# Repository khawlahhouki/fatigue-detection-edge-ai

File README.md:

#Real-Time Physical Fatigue Detection — Edge AI on STM32H7

> **Final Year Project (PFE) — ENICarthage, 2026**  
> Embedded Systems Engineering · In collaboration with Luleå University of Technology (LTU), Sweden

---

## Overview

A wearable embedded system for **real-time physical fatigue detection** using multimodal biosignals, running entirely on the edge — no cloud inference required.

The system acquires biosignals from 4 sensors, processes them in real-time under **FreeRTOS**, runs an **INT8 quantized ML model** via X-CUBE-AI, and transmits results to an admin dashboard via **LoRa**.

---

## System Architecture

```
┌─────────────────────────────────────────────────────┐
│                  STM32H7A3 @ 280 MHz                │
│                                                     │
│  ┌──────────┐  ┌──────────┐  ┌──────────────────┐   │
│  │ PPG/SpO2 │  │   IMU    │  │    EMG / ECG     │   │
│  │MAX86141  │  │ LSM6DSO  │  │    ADS1292R      │   │
│  └────┬─────┘  └────┬─────┘  └────────┬─────────┘   │
│       │              │                 │            │
│  ┌────▼──────────────▼─────────────────▼──────────┐ │
│  │           FreeRTOS Task Scheduler               ││
│  │  • Sensor Acquisition Tasks (IRQ + DMA)         ││
│  │  • NLMS Adaptive Filter (PPG artifact removal)  ││
│  │  • Feature Extraction (sliding window)          ││
│  │  • ML Inference Task (TFLite INT8 / X-CUBE-AI)  ││
│  │  • LoRa Transmission Task                       ││
│  └────────────────────────────────────────────────┘ │
└─────────────────────────────────────────────────────┘
         │
         │ LoRa
         ▼
   Admin Dashboard
```

---

## Sensors & Signals

| Sensor         | Signal              | Sampling Rate |
|----------------|---------------------|-------------- |
| MAX86141       | PPG / SpO2          | 400 Hz        |
| LSM6DSO        | IMU (Accel + Gyro)  | 104 Hz        |
| ADS1292R       | EMG / ECG           | 1000 Hz        |
| TMP117 / SHTC3 | Skin Temperature    | 1 Hz          |

## FreeRTOS Task Architecture

| Task | Priority | Description |
|------|----------|-------------|
| `TaskPPG` | High | MAX86141 acquisition via SPI + DMA |
| `TaskIMU` | High | LSM6DSO acquisition via SPI|
| `TaskEMG` | High | ADS1292R acquisition via SPI |
| `TaskTemp` | Low | TMP117/SHTC3 acquisition Via I2C|
| `TaskSync` | High | Temporal sync via TIM2 (µs timestamps) |
| `TaskFeatures| Medium | Sliding window feature extraction |
| `TaskInference| Medium | TFLite INT8 inference via X-CUBE-AI |
| `TaskLoRa` | Low | Fatigue result transmission |

---

##  Edge AI Pipeline

```
Raw Biosignals
     │
     ▼
Preprocessing (NLMS adaptive filter for PPG motion artifacts,
               bandpass filters for EMG)
     │
     ▼
Feature Extraction (sliding window — time + frequency domain)
     │
     ▼
TFLite INT8 Model (CNN-TCN architecture)
quantized & deployed via X-CUBE-AI
     │
     ▼
Fatigue Label: [Normal | Moderate | High]
```

- **Model architecture:** CNN-TCN (Temporal Convolutional Network)
- **Quantization:** INT8 post-training quantization
- **Deployment tool:** ST X-CUBE-AI / ST Edge AI Core
- **Validation:** LOSO cross-validation (Leave-One-Subject-Out)

---

##  LoRa Communication

Fatigue detection results and vital signs are transmitted wirelessly to an **admin dashboard** using LoRa, enabling remote monitoring without WiFi/cellular infrastructure — ideal for industrial or outdoor environments.

---

##  Hardware

- **MCU:** STM32H7A3ZIT6 @ 280 MHz (Cortex-M7)
- **Custom PCB:** Designed for wearable form factor (includes all 4 sensors + LoRa module)
- **Memory:** DTCMRAM (512KB) · AXI-SRAM (1MB) · Flash (2MB)

---

##  Tech Stack

| Layer | Technologies |
|-------|-------------|
| Firmware | C / C++, STM32CubeIDE, HAL, bare-metal drivers |
| RTOS | FreeRTOS (tasks, semaphores, DMA sync) |
| Signal Processing | NLMS adaptive filter, bandpass FIR/IIR |
| ML Training | Python, TensorFlow/Keras, TFLite |
| Edge Deployment | X-CUBE-AI, ST Edge AI Core, INT8 quantization |
| Communication | LoRa (UART), SPI, I2C, DMA |
| PCB Design | KiCad |

---

## Repository Structure

```
fatigue-detection-edge-ai/
├── Core/
│   ├── Src/              # Main application + FreeRTOS tasks
│   └── Inc/              # Headers
├── Drivers/
│   ├── MAX86141/         # PPG/SpO2 driver
│   ├── LSM6DSO/          # IMU driver
│   ├── ADS1292R/         # EMG/ECG driver
│   └── TMP117/           # Temperature driver
├── Middlewares/
│   └── Third_Party/FreeRTOS/
├── ML/                   # TFLite model + X-CUBE-AI generated files
├── PCB/                  # Schematics and PCB layout
└── Acquisition_Biosignaux.ioc  # STM32CubeMX config
```

---

##  Current Status

- [x] FreeRTOS task architecture
- [x] MAX86141 PPG/SpO2 driver (SPI + DMA)
- [x] ADS1292R EMG/ECG driver
- [x] LSM6DSO IMU driver
- [x] NLMS adaptive filter for PPG motion artifact removal
- [x] Temporal synchronization (TIM2 µs timestamps)
- [x]  Feature extraction pipeline
- [x]  ML model training & quantization 
- [x]  LoRa transmission task 
- [x]  PCB fabrication & testing 

---

## Author

**Khaoula Houki**  
Embedded Systems Engineer — ENICarthage  
---

## Academic Context

- **Institution:** École Nationale d'Ingénieurs de Carthage (ENICarthage), Tunisia
- **Research Partner:** Luleå University of Technology (LTU), Sweden
- **Year:** 2025–2026

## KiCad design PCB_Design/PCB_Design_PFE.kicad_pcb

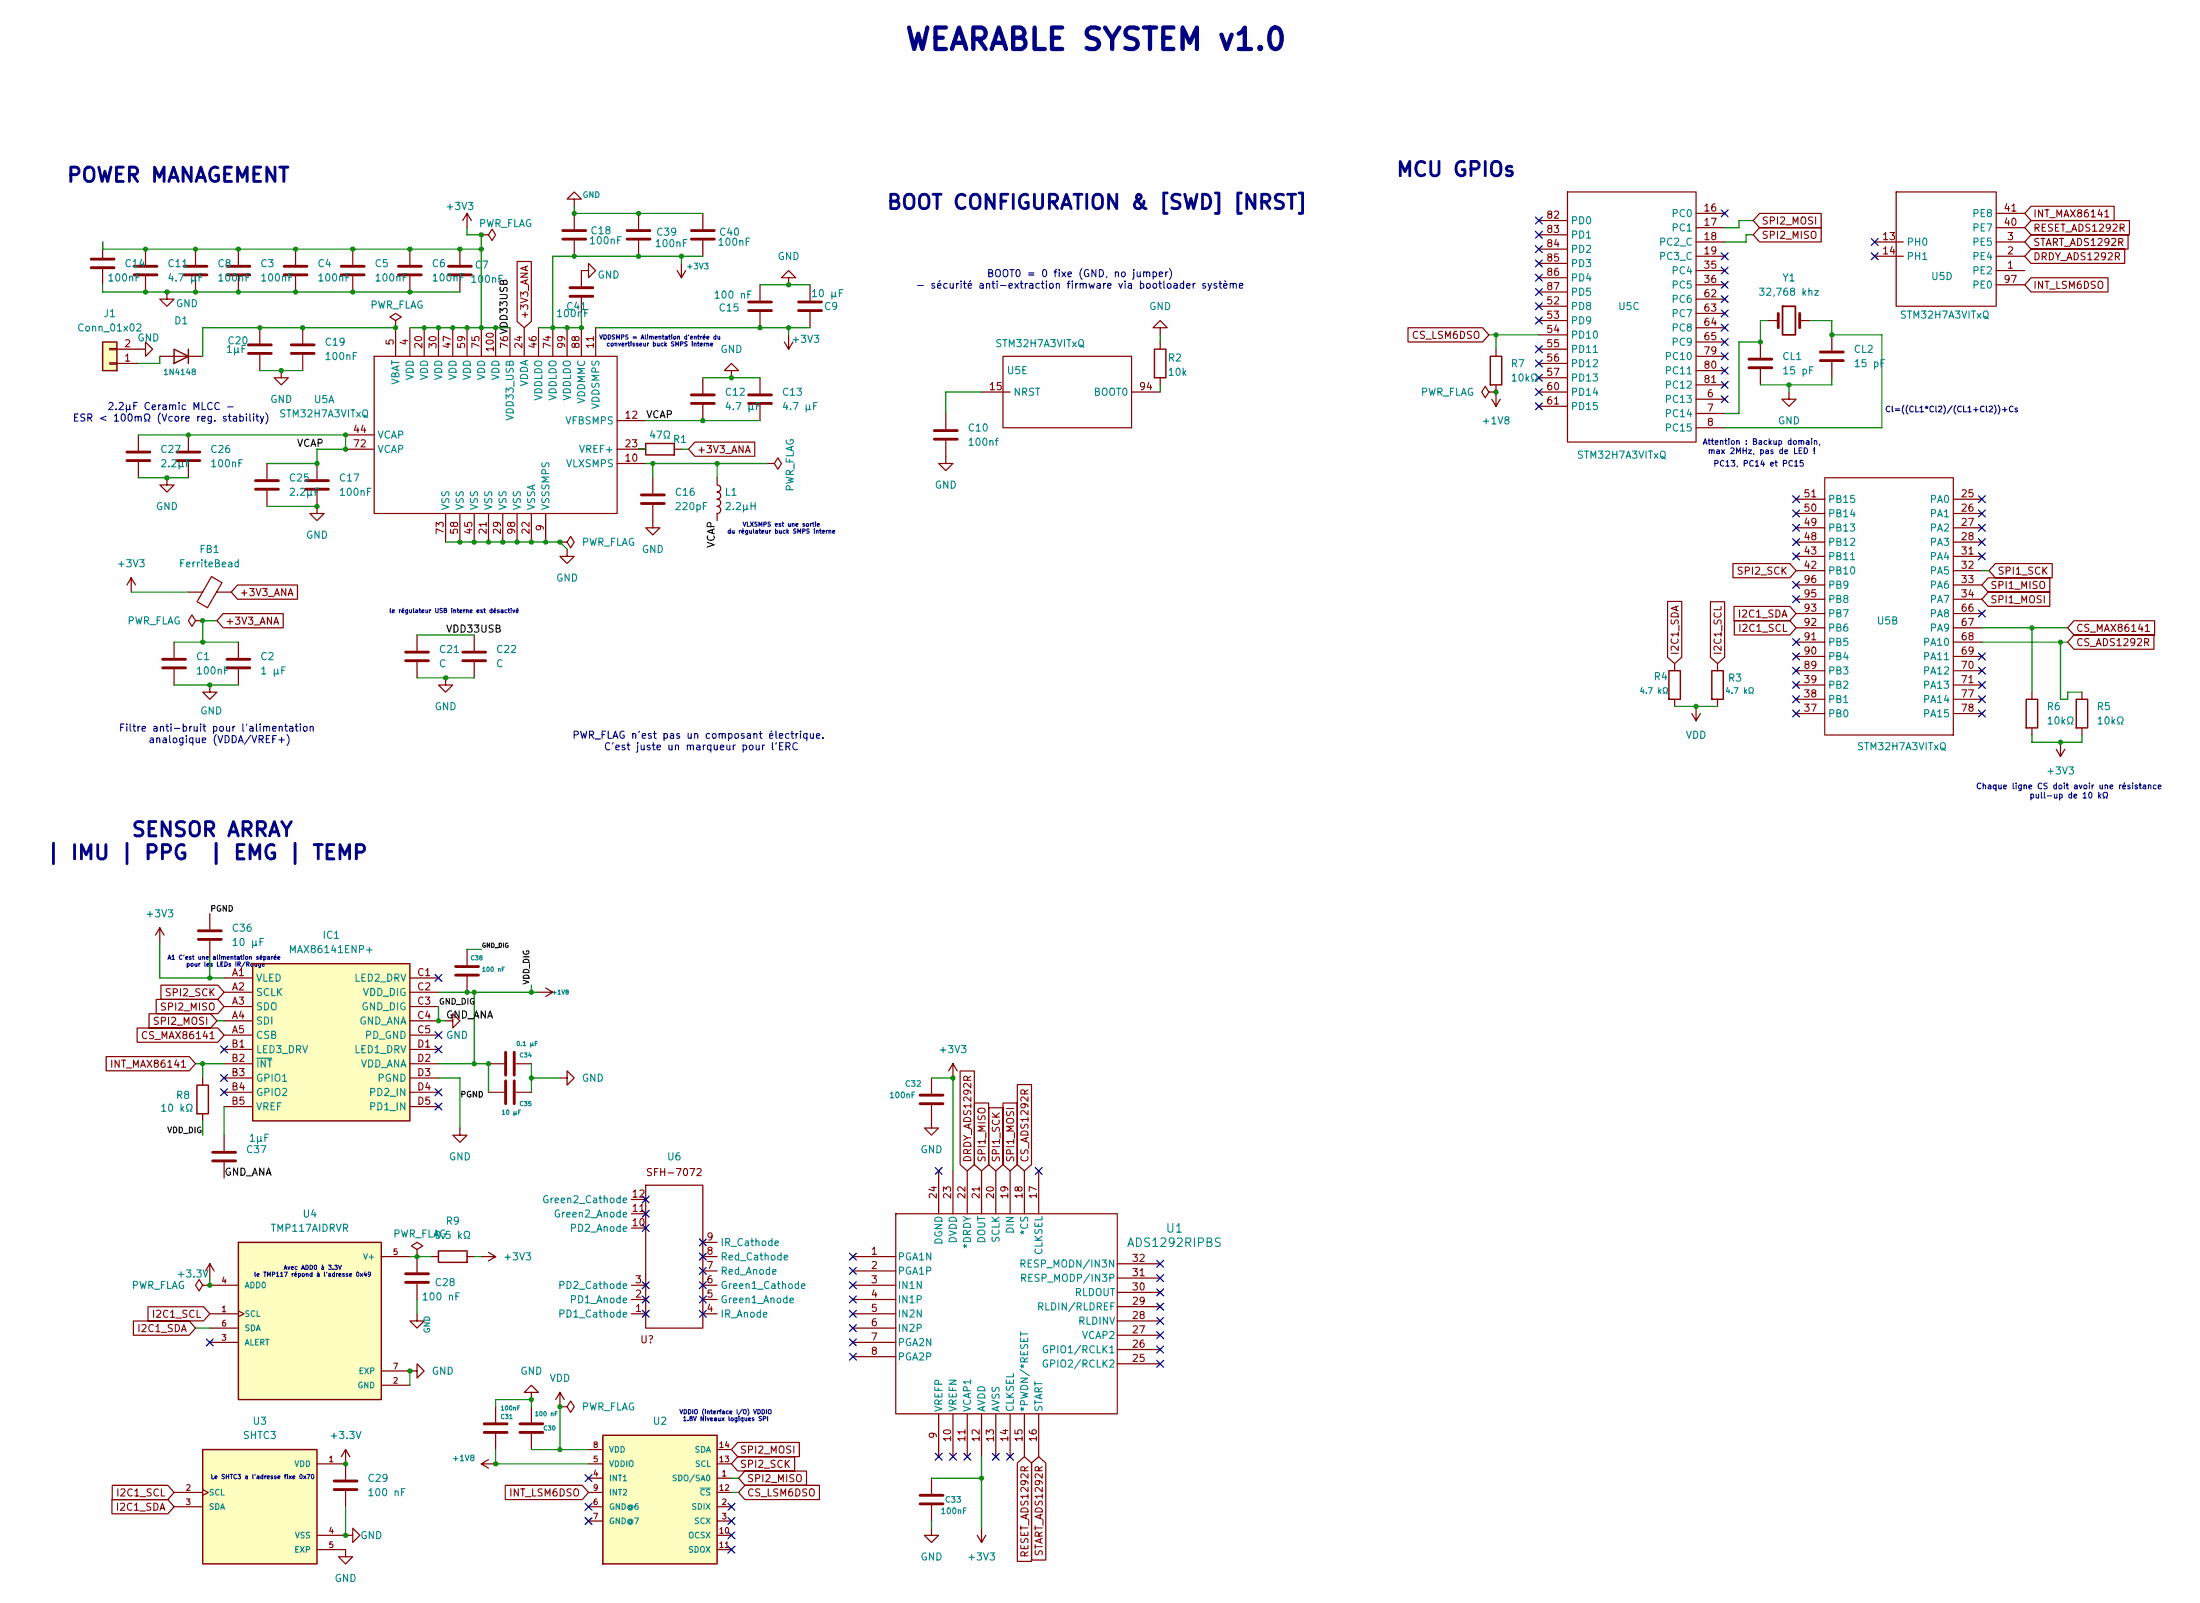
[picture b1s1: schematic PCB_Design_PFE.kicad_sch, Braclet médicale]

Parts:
C1, C3, C4, C5, C6, C7, C8, C14, C17, C18, C19, C26, C31, C32, C33, C39, C40, C41: 100nF; C_0603_1608Metric
C2: 1 µF; C_0603_1608Metric
C9, C35, C36: 10 μF; C_0603_1608Metric
C10: 100nf; C_0603_1608Metric
C11: 4.7 µF; C_0603_1608Metric
C12, C13: 4.7 μF; C_1206_3216Metric
C15, C28, C29, C30, C38: 100 nF; C_0603_1608Metric
C16: 220pF; C_0402_1005Metric
C20: 1µF; C_0603_1608Metric
C21, C22: C; C_0603_1608Metric
C25, C27: 2.2µF; C_0603_1608Metric
C34: 0.1 μF; C_0603_1608Metric
C37: 1μF; C_0603_1608Metric
CL1, CL2: 15 pF; C_0402_1005Metric
D1: 1N4148; D_SOD-123
FB1: FerriteBead; R_0603_1608Metric
IC1: MAX86141ENP+; BGA20C40P5X4_205X185X50; Manufacturer_Part_Number MAX86141ENP+; Mouser Part Number 700-MAX86141ENP+
J1: Conn_01x02; D_SOD-123
L1: 2.2µH; L_0603_1608Metric
R1: 47Ω; R_0603_1608Metric
R2: 10k; R_0603_1608Metric
R3, R4: 4.7 kΩ; R_0603_1608Metric
R5, R6, R7: 10kΩ; R_0603_1608Metric
R8: 10 kΩ; R_0603_1608Metric
R9: 0.5 kΩ; R_0603_1608Metric
U1: ADS1292RIPBS; PBS32
U2: LSM6DSOX; LGA14L
U3: SHTC3; SON100P200X200X80-5N; PARTREV 3
U4: TMP117AIDRVR; SON65P200X200X80-7N; PARTREV B
U5: STM32H7A3VITxQ; LQFP-100_14x14mm_P0.5mm
U6: SFH-7072_Optical
Y1: 32,768 khz; Crystal_SMD_3215-2Pin_3.2x1.5mm

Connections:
+1V8: C31.2, C34.1, C35.1, C38.2, IC1.C2 (VDD_DIG), IC1.D2 (VDD_ANA), R7.2, R8.2, U2.5 (VDDIO)
+3.3V: C29.1, U3.1 (VDD), U4.4 (ADD0)
+3V3: C3.1, C4.1, C5.1, C6.1, C7.1, C8.1, C9.1, C11.1, C14.1, C15.1, C18.2, C32.1, C33.1, C36.2, C39.2, C40.2, C41.2, FB1.1, IC1.A1 (VLED), R5.2, R6.2, R9.2, U1.12 (AVDD), U1.23 (DVDD), U5.4 (VDD), U5.11 (VDDSMPS), U5.20 (VDD), U5.30 (VDD), U5.46 (VDDLDO), U5.47 (VDD), U5.59 (VDD), U5.74 (VDDLDO), U5.75 (VDD), U5.76 (VDD33_USB), U5.88 (VDDMMC), U5.99 (VDDLDO), U5.100 (VDD); also elsewhere on the board
+3V3_ANA: C1.1, C2.1, FB1.2, R1.2, U5.24 (VDDA)
/VCAP: C12.2, C13.2, C17.1, C25.1, C26.1, C27.1, L1.2, U5.12 (VFBSMPS), U5.44 (VCAP), U5.72 (VCAP)
/VDD33USB: C21.1, C22.1
CS_ADS1292R: R5.1, U1.18 (*CS), U5.68 (PA10)
CS_LSM6DSO: R7.1, U2.12 (~CS), U5.54 (PD10)
CS_MAX86141: IC1.A5 (CSB), R6.1, U5.67 (PA9)
DRDY_ADS1292R: U1.22 (*DRDY), U5.2 (PE4)
GND: C1.2, C2.2, C3.2, C4.2, C5.2, C6.2, C7.2, C8.2, C9.2, C10.2, C11.2, C12.1, C13.1, C14.2, C15.2, C16.2, C17.2, C18.1, C19.2, C20.2, C21.2, C22.2, C25.2, C26.2, C27.2, C28.2, C29.2, C30.1, C31.1, C32.2, C33.2, C34.2, C35.2, C36.1, C37.2, C38.1, C39.1, C40.1, C41.1, CL1.2, CL2.2, IC1.C3 (GND_DIG), IC1.C4 (GND_ANA), IC1.D3 (PGND), J1.2, R2.1, U3.4 (VSS), U3.5 (EXP), U4.2 (GND), U4.7 (EXP), U5.9 (VSSSMPS), U5.21 (VSS), U5.22 (VSSA), U5.29 (VSS), U5.45 (VSS), U5.58 (VSS), U5.73 (VSS), U5.98 (VSS); also elsewhere on the board
I2C1_SCL: R3.1, U3.2 (SCL), U4.1 (SCL), U5.92 (PB6)
I2C1_SDA: R4.1, U3.3 (SDA), U4.6 (SDA), U5.93 (PB7)
INT_LSM6DSO: U2.9 (INT2), U5.97 (PE0)
INT_MAX86141: IC1.B2 (~INT), R8.1, U5.1 (PE2), U5.41 (PE8)
unnamed: D1.2 (A), J1.1
unnamed: C19.1, C20.1, D1.1 (K), U5.5 (VBAT)
unnamed: C37.1, IC1.B5 (VREF)
unnamed: C28.1, R9.1, U4.5 (V+)
unnamed: C16.1, L1.1, U5.10 (VLXSMPS)
unnamed: R1.1, U5.23 (VREF+)
unnamed: CL1.1, U5.7 (PC14), Y1.1
unnamed: CL2.1, U5.8 (PC15), Y1.2
unnamed: R2.2, U5.94 (BOOT0)
unnamed: C10.1, U5.15 (NRST)
RESET_ADS1292R: U1.15 (*PWDN/*RESET), U5.40 (PE7)
SPI1_MISO: U1.21 (DOUT), U5.33 (PA6)
SPI1_MOSI: U1.19 (DIN), U5.34 (PA7)
SPI1_SCK: U1.20 (SCLK), U5.32 (PA5)
SPI2_MISO: IC1.A3 (SDO), U2.1 (SDO/SA0), U5.18 (PC2_C)
SPI2_MOSI: IC1.A4 (SDI), U2.14 (SDA), U5.17 (PC1)
SPI2_SCK: IC1.A2 (SCLK), U2.13 (SCL), U5.42 (PB10)
START_ADS1292R: U1.16 (START), U5.3 (PE5)
VDD: C30.2, R3.2, R4.2, U2.8 (VDD)

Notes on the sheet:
BOOT0 = 0 fixe (GND, no jumper) - sécurité anti-extraction firmware via bootloader système
Attention : Backup domain, max 2MHz, pas de LED !
Cl=((CL1*Cl2)/(CL1+Cl2))+Cs
2.2µF Ceramic MLCC - ESR < 100mΩ (Vcore reg. stability)
Chaque ligne CS doit avoir une résistance pull-up de 10 kΩ
BOOT CONFIGURATION & [SWD] [NRST]
VDDIO (interface I/O) VDDIO 1.8V Niveaux logiques SPI
MCU GPIOs
WEARABLE SYSTEM v1.0
VLXSMPS est une sortie du régulateur buck SMPS interne
Filtre anti-bruit pour l'alimentation analogique (VDDA/VREF+)
PC13, PC14 et PC15
A1 C'est une alimentation séparée pour les LEDs IR/Rouge
SENSOR ARRAY | IMU | PPG | EMG | TEMP
Avec ADD0 à 3.3V le TMP117 répond à l'adresse 0x49
VDDSMPS = Alimentation d'entrée du convertisseur buck SMPS interne
POWER MANAGEMENT
PWR_FLAG n'est pas un composant électrique. C'est juste un marqueur pour l'ERC
Le SHTC3 a l'adresse fixe 0x70
le régulateur USB interne est désactivé

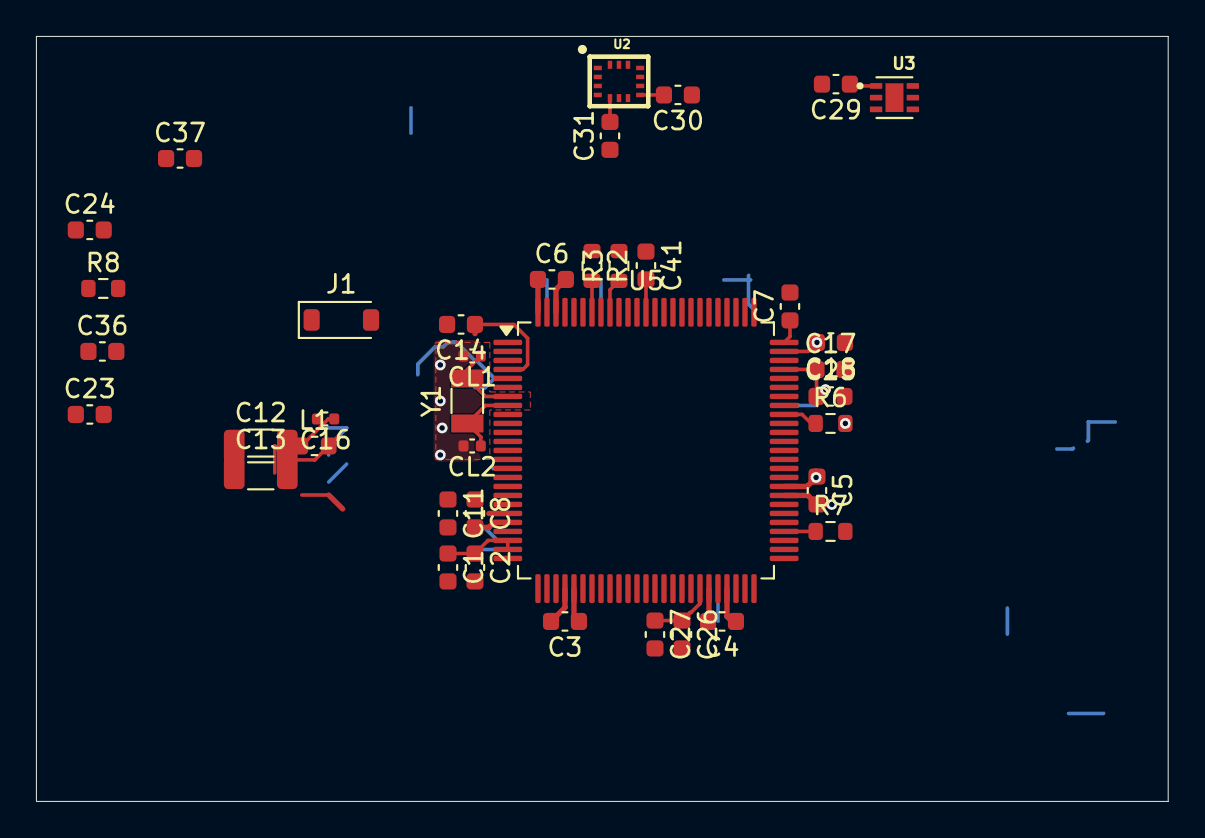
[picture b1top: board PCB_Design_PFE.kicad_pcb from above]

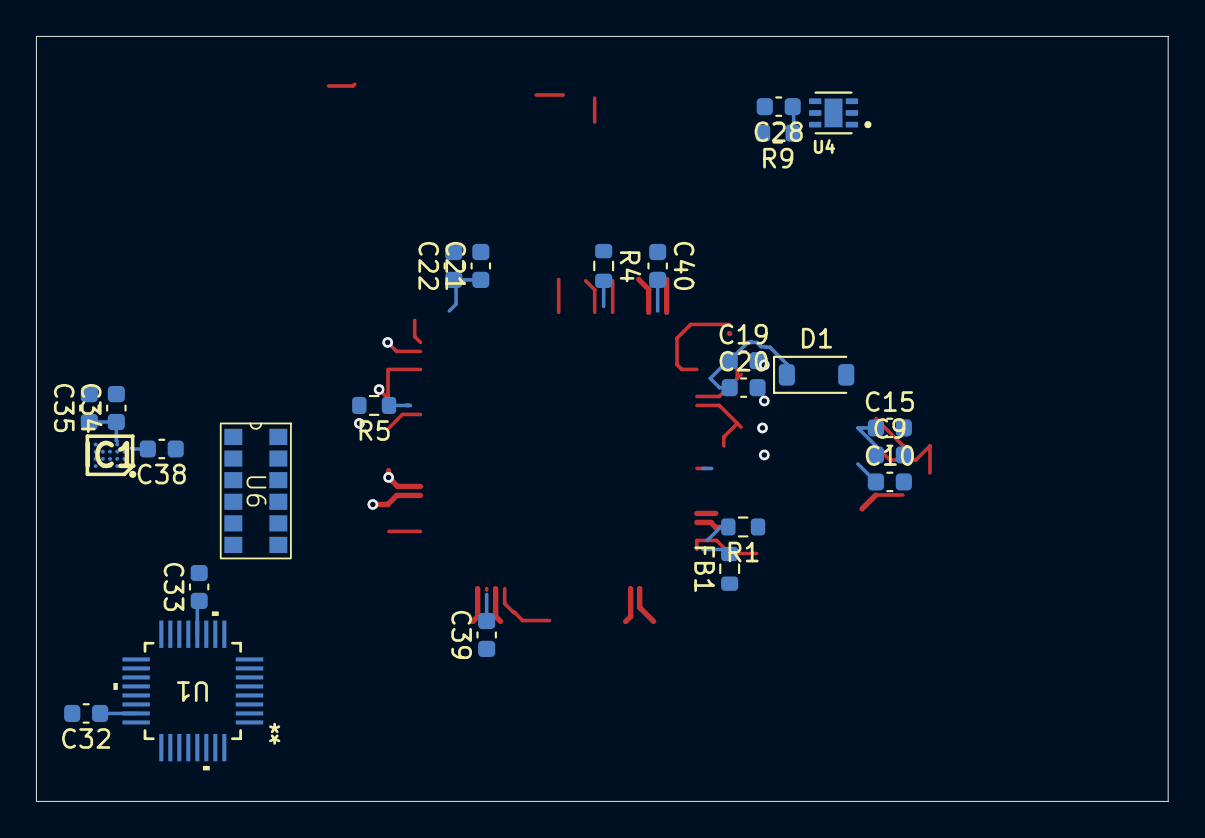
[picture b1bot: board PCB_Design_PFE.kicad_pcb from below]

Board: 4 copper layers, 62.9 x 42.5 mm, 64 parts (25 on the bottom side), 34 nets.

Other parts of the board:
C23: 1µF; C_0603_1608Metric
C24: 100nF; C_0603_1608Metric

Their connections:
+3V3: C23.1, C24.1; also elsewhere on the board
GND: C23.2, C24.2; also elsewhere on the board

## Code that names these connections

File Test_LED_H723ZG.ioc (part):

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Mcu.Name=STM32H723ZGTx
Mcu.Package=LQFP144
Mcu.UserName=STM32H723ZGTx
PA0.GPIOParameters=GPIO_Speed,PinState,GPIO_Label
PA0.GPIO_Label=CS_EMG
PA0.GPIO_Speed=GPIO_SPEED_FREQ_HIGH
PA0.PinState=GPIO_PIN_SET
PA0.Signal=GPIO_Output
PA13(JTMS/SWDIO).GPIOParameters=GPIO_Label
PA13(JTMS/SWDIO).GPIO_Label=SWDIO
PA13(JTMS/SWDIO).Signal=DEBUG_JTMS-SWDIO
PA14(JTCK/SWCLK).GPIOParameters=GPIO_Label
PA14(JTCK/SWCLK).GPIO_Label=SWCLK
PA14(JTCK/SWCLK).Signal=DEBUG_JTCK-SWCLK
PA5.Mode=Full_Duplex_Master
PA5.Signal=SPI1_SCK
PA6.Mode=Full_Duplex_Master
PA6.Signal=SPI1_MISO
PA7.Mode=Full_Duplex_Master
PA7.Signal=SPI1_MOSI
PA9.GPIOParameters=GPIO_Speed,PinState,GPIO_Label
PA9.GPIO_Label=CS_PPG
PA9.GPIO_Speed=GPIO_SPEED_FREQ_HIGH
PA9.PinState=GPIO_PIN_SET
PA9.Signal=GPIO_Output
PB0.Signal=GPIO_Output
PB10.Mode=Full_Duplex_Master
PB10.Signal=SPI2_SCK
PB14.Signal=GPIO_Output
PB6.Mode=I2C
PB6.Signal=I2C1_SCL
PB7.Mode=I2C
PB7.Signal=I2C1_SDA
PC1.Mode=Full_Duplex_Master
PC1.Signal=SPI2_MOSI
PC10.Mode=Full_Duplex_Master
PC10.Signal=SPI3_SCK
PC11.Mode=Full_Duplex_Master
PC11.Signal=SPI3_MISO
PC12.Mode=Full_Duplex_Master
PC12.Signal=SPI3_MOSI
PC13.Signal=GPIO_Input
PC14-OSC32_IN.Signal=RCC_OSC32_IN
PC15-OSC32_OUT.Signal=RCC_OSC32_OUT
PC2_C.Mode=Full_Duplex_Master
PC2_C.Signal=SPI2_MISO
PC8.GPIOParameters=PinState,GPIO_Label
PC8.GPIO_Label=NRESET
PC8.PinState=GPIO_PIN_SET
PC8.Signal=GPIO_Output
PC9.GPIOParameters=PinState,GPIO_Label
PC9.GPIO_Label=NSS
PC9.PinState=GPIO_PIN_SET
PC9.Signal=GPIO_Output
PD0.GPIOParameters=GPIO_PuPd,GPIO_Label
PD0.GPIO_Label=INT1_IMU
PD0.GPIO_PuPd=GPIO_PULLDOWN
PD0.Signal=GPXTI0
PD12.Mode=I2C
PD12.Signal=I2C4_SCL
PD13.Mode=I2C
PD13.Signal=I2C4_SDA
PD8.Signal=USART3_TX
PD9.Signal=USART3_RX
PE1.Signal=GPIO_Output
PE13.Mode=Full_Duplex_Master
PE13.Signal=SPI4_MISO
PE2.Mode=Full_Duplex_Master
PE2.Signal=SPI4_SCK
PE4.GPIOParameters=GPIO_PuPd,GPIO_Label
PE4.GPIO_Label=DRDY_EMG
PE4.GPIO_PuPd=GPIO_PULLUP
PE4.Signal=GPXTI4
PE5.GPIOParameters=GPIO_Label
PE5.GPIO_Label=START_EMG
PE5.Signal=GPIO_Output
PE6.Mode=Full_Duplex_Master
PE6.Signal=SPI4_MOSI
PE7.GPIOParameters=GPIO_Label
PE7.GPIO_Label=RESET_EMG
PE7.Signal=GPIO_Output
PE8.GPIOParameters=GPIO_PuPd,GPIO_Label,GPIO_ModeDefaultEXTI
PE8.GPIO_Label=INT_PPG
PE8.GPIO_ModeDefaultEXTI=GPIO_MODE_IT_FALLING
PE8.GPIO_PuPd=GPIO_PULLUP
PE8.Signal=GPXTI8
PF1.GPIOParameters=GPIO_Label
PF1.GPIO_Label=DIO0
PF1.Signal=GPXTI1
PG14.GPIOParameters=GPIO_Speed,PinState,GPIO_PuPd,GPIO_Label
PG14.GPIO_Label=CS_IMU
PG14.GPIO_PuPd=GPIO_PULLUP
PG14.GPIO_Speed=GPIO_SPEED_FREQ_HIGH
PG14.PinState=GPIO_PIN_SET
PG14.Signal=GPIO_Output
RCC.HSE_VALUE=8000000
RCC.SYSCLKFreq_VALUE=275000000
RCC.SYSCLKSource=RCC_SYSCLKSOURCE_PLLCLK
board=NUCLEO-H723ZG
boardIOC=true

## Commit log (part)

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2026-04-15 Add FREERTOS DSP Task
2026-06-01 Update firmware FreeRTOS + PCB KiCad design
